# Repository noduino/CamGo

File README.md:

# CamGo
Smart Home Dog to monitor 315&433MHz Sensors, Switches ...

Sensors:

  * door open sensor
  * wireless door bell
  * smoke detection (wireless alarm)
  * gas detection (wireless alarm)
  * wind & rain sensor
  ......

Switchs:

  * 315/433 light switch
  * dooya curtion
  * automatic window
  ......

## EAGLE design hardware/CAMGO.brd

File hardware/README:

Copyright 2015 MaiKe Labs

These files are part of CamGo.

This is a free hardware design; you can redistribute it and/or modify
it under the terms of the GNU General Public License as published by
the Free Software Foundation; either version 2, or (at your option)
any later version.

This design is distributed in the hope that it will be useful,
but WITHOUT ANY WARRANTY; without even the implied warranty of
MERCHANTABILITY or FITNESS FOR A PARTICULAR PURPOSE.  See the
GNU General Public License for more details.

You should have received a copy of the GNU General Public License
along with this design; see the file COPYING.  If not, write to
the Free Software Foundation, Inc., 51 Franklin Street,
Boston, MA 02110-1301, USA.

CamGo is a Smart Home Gateway for 315MHz, 433MHz Sensors and Switches 

hardware notes:

Schematic and layout files were designed in Eagle.

PCB description: 2 layer PCB 0.062 in
    Copper        1   0.5 oz foil plated to approximately 0.0017 in
    Copper        2   0.5 oz foil plated to approximately 0.0017 in

FR4 or similar substrate with Er=4.5 (+/- 0.1)
double side solder mask green
single side silkscreen white
6 mil min trace width and
6 mil min isolation

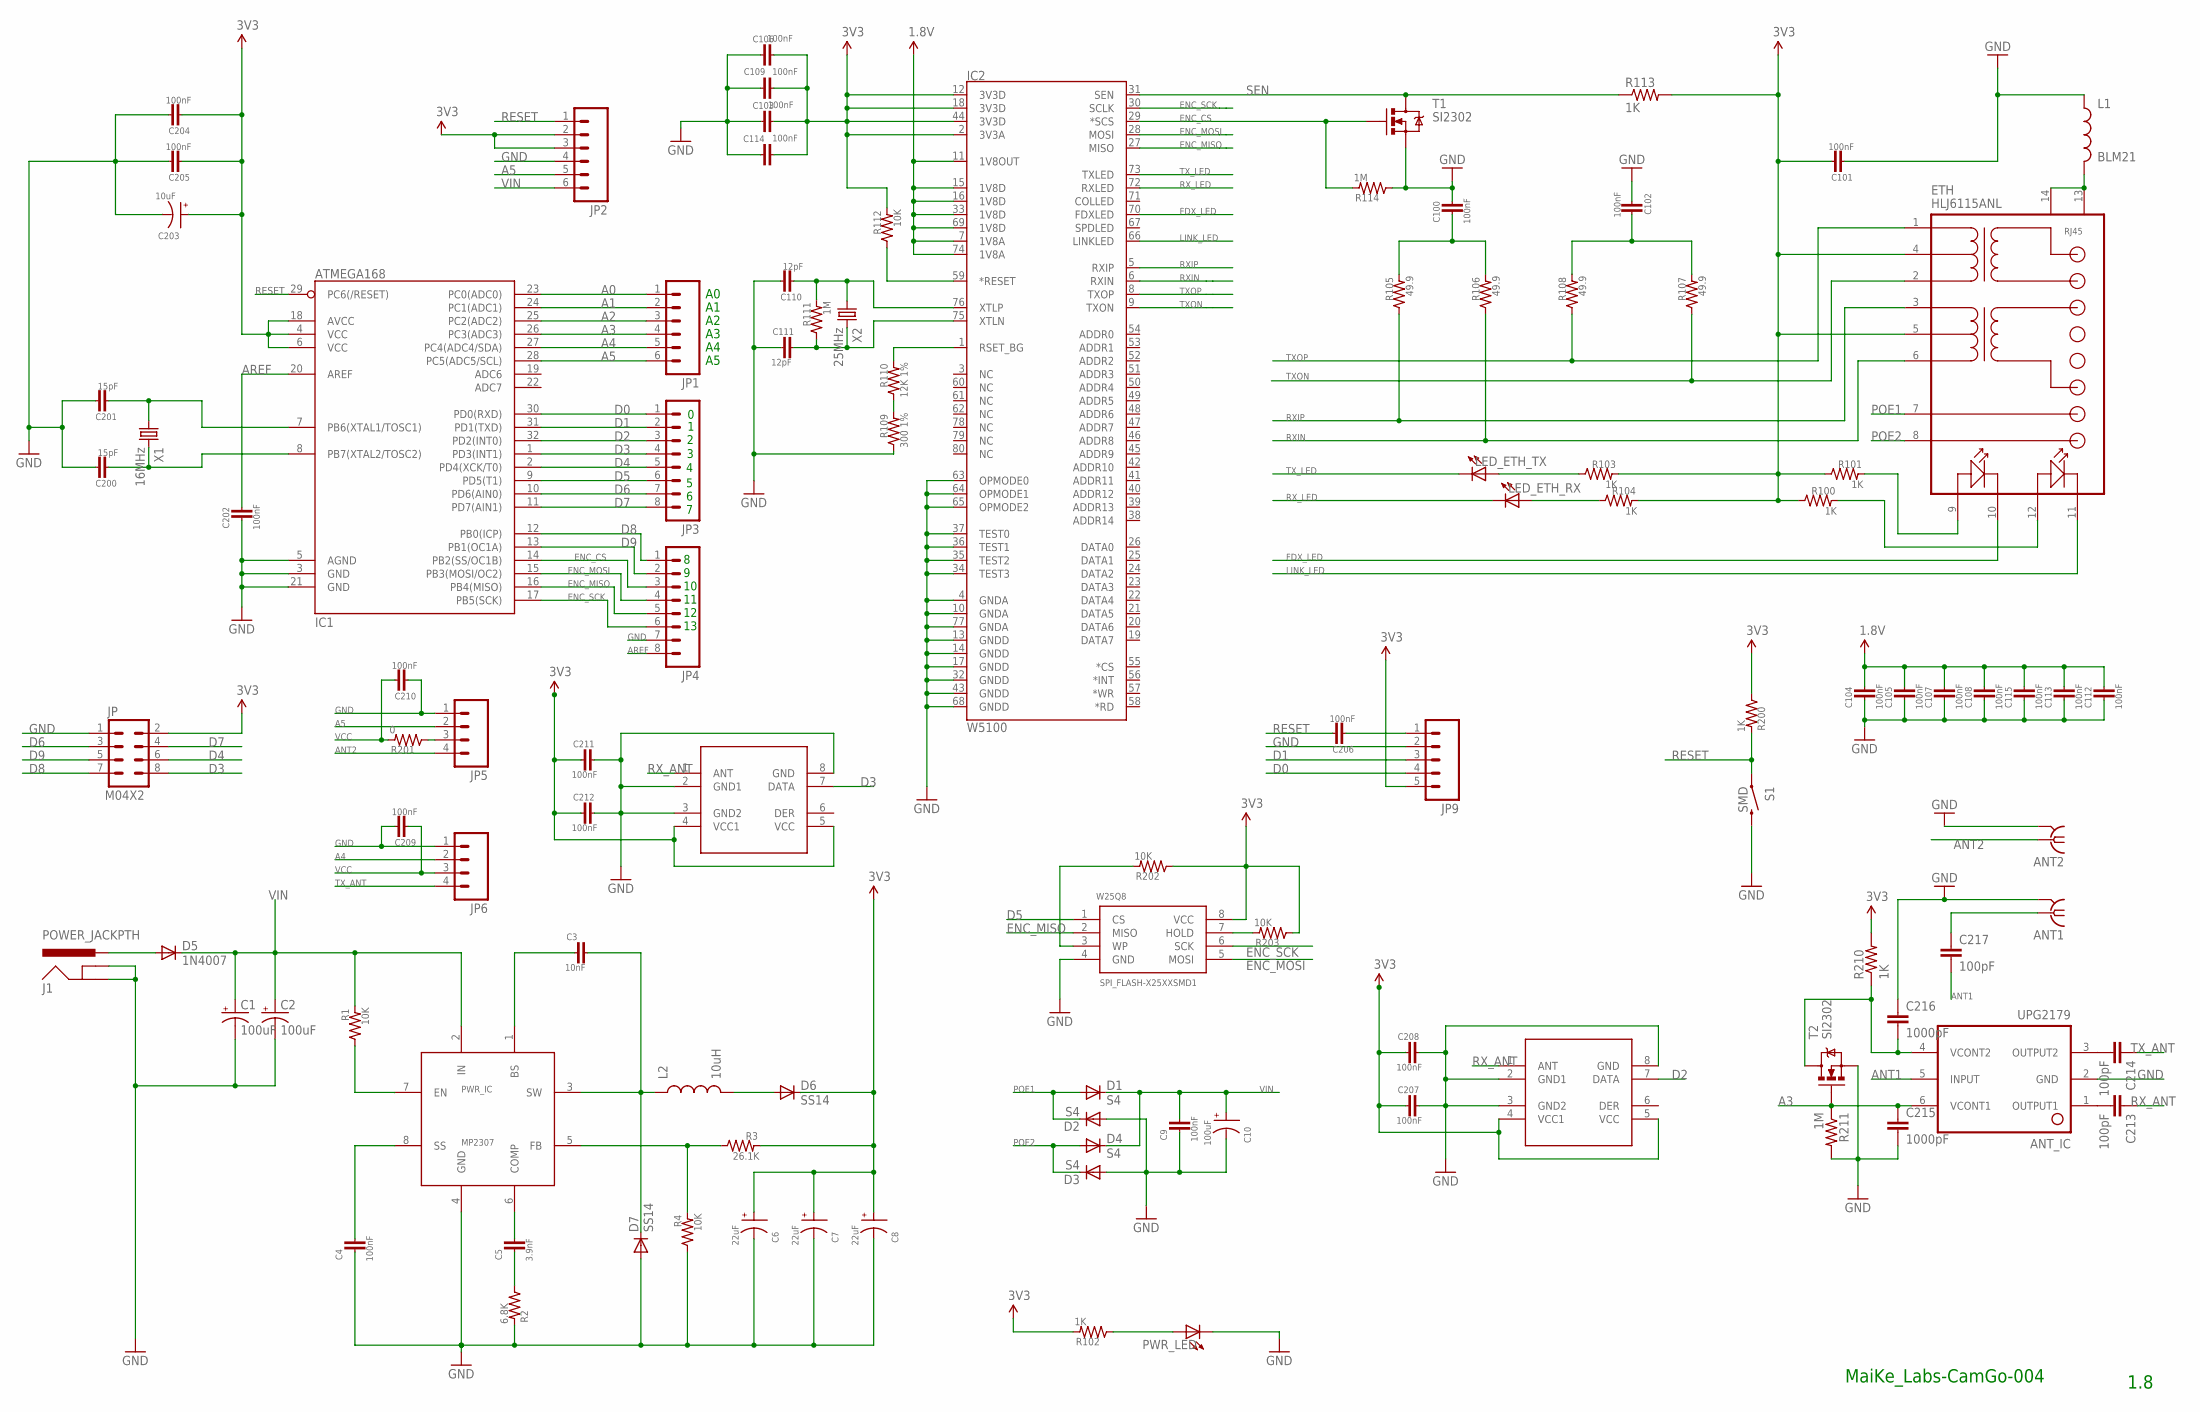
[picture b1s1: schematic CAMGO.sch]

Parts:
ANT1, ANT2: SMA--KE; SMA-KE
ANT_IC: UPG2179; SOT363
C1, C2, C10: 100uF; NIPPON_F80
C3: 10nF; 0603-CAP
C4, C9, C100, C101, C102, C103, C104, C105, C106, C107, C108, C109, C112, C113, C114, C115, C202, C204, C205, C206, C207, C208, C209, C210, C211, C212: 100nF; 0603-CAP
C5: 3.9nF; 0603-CAP
C6, C7, C8: 22uF; EIA3216
C110, C111: 12pF; 0603-CAP
C200, C201: 15pF; 0603-CAP
C203: 10uF; EIA3216
C213, C214, C217: 100pF; 0603-CAP
C215, C216: 1000pF; 0603-CAP
D1, D2, D3, D4: S4; SOD-323
D5: 1N4007; SMB-DIODE
D6, D7: SS14; SOD-323
ETH: HLJ6115ANL; HR911105A
IC1: ATMEGA168; TQFP32-08
IC2: W5100; LQFP-80
J1: POWER_JACKPTH; POWER_JACK_PTH
JP: M04X2; 2X4
JP1, JP2: M06SIP; 1X06
JP3, JP4: M081X08; 1X08
JP5, JP6: M04PTH; 1X04
JP9: M05PTH; 1X05
L1: BLM21; 0805
L2: 10uH; CR54
LED_ETH_RX: LED0603; LED-0603
LED_ETH_TX: LED0603; LED-0603
PWR_IC: MP2307; SOIC8
PWR_LED: LED0603; LED-0603
R1, R4, R112, R202, R203: 10K; 0603-RES
R2: 6.8K; 0603-RES
R3: 26.1K; 0603-RES
R100, R101, R102, R103, R104, R113, R200, R210: 1K; 0603-RES
R105, R106, R107, R108: 49.9; 0603-RES
R109: 300 1%; 0603-RES
R110: 12K 1%; 0603-RES
R111, R114, R211: 1M; 0603-RES
R201: 0; 0603-RES
RX_IC1, RX_IC2: RXB6-MODULE
S1: SMD; TACTILE-SWITCH-1101NE
T1, T2: SI2302; SOT23-3
W25Q8: SPI_FLASH-X25XXSMD1; SO08-EIAJ
X1: 16MHz; HC49US
X2: 25MHz; HC49US

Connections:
1.8V: C104.1, C105.1, C107.1, C108.1, C112.1, C113.1, C115.1, IC2.7 (1V8A), IC2.11 (1V8OUT), IC2.15 (1V8D), IC2.16 (1V8D), IC2.33 (1V8D), IC2.69 (1V8D), IC2.74 (1V8A)
A0: IC1.23 (PC0(ADC0)), JP1.1
A1: IC1.24 (PC1(ADC1)), JP1.2
A2: IC1.25 (PC2(ADC2)), JP1.3
A3: ANT_IC.6 (VCONT1), C215.1, IC1.26 (PC3(ADC3)), JP1.4, R211.1, T2.1 (G)
A4: IC1.27 (PC4(ADC4/SDA)), JP1.5, JP6.2
A5: IC1.28 (PC5(ADC5/SCL)), JP1.6, JP2.5, JP5.2
ANT1: ANT_IC.5 (INPUT), C217.2
ANT2: ANT2.1, JP5.4
AREF: C202.1, IC1.20 (AREF), JP4.8
D0: IC1.30 (PD0(RXD)), JP3.1, JP9.4
D1: IC1.31 (PD1(TXD)), JP3.2, JP9.3
D2: IC1.32 (PD2(INT0)), JP3.3, RX_IC1.7 (DATA)
D3: IC1.1 (PD3(INT1)), JP.8, JP3.4, RX_IC2.7 (DATA)
D4: IC1.2 (PD4(XCK/T0)), JP.6, JP3.5
D5: IC1.9 (PD5(T1)), JP3.6, W25Q8.1 (CS)
D6: IC1.10 (PD6(AIN0)), JP.3, JP3.7
D7: IC1.11 (PD7(AIN1)), JP.4, JP3.8
D8: IC1.12 (PB0(ICP)), JP.7, JP4.1
D9: IC1.13 (PB1(OC1A)), JP.5, JP4.2
ENC_CS: IC1.14 (PB2(SS/OC1B)), IC2.29 (*SCS), JP4.3, R114.2, T1.1 (G)
ENC_MISO: IC1.16 (PB4(MISO)), IC2.27 (MISO), JP4.5, W25Q8.2 (MISO)
ENC_MOSI: IC1.15 (PB3(MOSI/OC2)), IC2.28 (MOSI), JP4.4, W25Q8.5 (MOSI)
ENC_SCK: IC1.17 (PB5(SCK)), IC2.30 (SCLK), JP4.6, W25Q8.6 (SCK)
FDX_LED: ETH.10, IC2.70 (FDXLED)
GND: ANT1.G@1 (GND), ANT1.G@2 (GND), ANT1.G@3 (GND), ANT1.G@4 (GND), ANT2.G@1 (GND), ANT2.G@2 (GND), ANT2.G@3 (GND), ANT2.G@4 (GND), ANT_IC.2 (GND), C1.-, C2.-, C4.2, C6.C (-), C7.C (-), C8.C (-), C9.2, C10.-, C100.1, C101.2, C102.2, C103.2, C104.2, C105.2, C106.2, C107.2, C108.2, C109.1, C110.1, C111.2, C112.2, C113.2, C114.1, C115.2, C200.1, C201.1, C202.2, C203.C (-), C204.1, C205.1, C207.1, C208.1, C209.1, C210.2, C211.1, C212.1, C215.2, C216.1, D2.2 (A), D3.2 (A), D7.2 (A), IC1.3 (GND), IC1.5 (AGND), IC1.21 (GND), IC2.4 (GNDA), IC2.10 (GNDA), IC2.13 (GNDD), IC2.14 (GNDD), IC2.17 (GNDD), IC2.32 (GNDD), IC2.34 (TEST3), IC2.35 (TEST2), IC2.36 (TEST1), IC2.37 (TEST0), IC2.43 (GNDD), IC2.63 (OPMODE0), IC2.64 (OPMODE1), IC2.65 (OPMODE2), IC2.68 (GNDD), IC2.77 (GNDA), J1.GND, J1.GNDBREAK, JP.1, JP2.4, JP4.7, JP5.1, JP6.1, JP9.2, L1.1, PWR_IC.4 (GND), PWR_LED.C, R2.2, R4.1, R109.1, R114.1, R211.2, RX_IC1.2 (GND1), RX_IC1.3 (GND2), RX_IC1.8 (GND), RX_IC2.2 (GND1), RX_IC2.3 (GND2), RX_IC2.8 (GND), S1.P$2 (2), T1.2 (S), T2.2 (S), W25Q8.4 (GND)
LINK_LED: ETH.11, IC2.66 (LINKLED)
unnamed: ETH.9, R101.2
unnamed: C201.2, IC1.7 (PB6(XTAL1/TOSC1)), X1.1
unnamed: C200.2, IC1.8 (PB7(XTAL2/TOSC2)), X1.2
unnamed: C110.2, IC2.76 (XTLP), R111.2, X2.1
unnamed: R202.2, W25Q8.3 (WP)
unnamed: C206.2, JP9.1
unnamed: D5.A, J1.PWR
unnamed: C111.1, IC2.75 (XTLN), R111.1, X2.2
unnamed: C3.2, PWR_IC.1 (BS)
unnamed: PWR_IC.7 (EN), R1.1
unnamed: PWR_LED.A, R102.1
unnamed: C4.1, PWR_IC.8 (SS)
unnamed: IC2.1 (RSET_BG), R110.2
unnamed: R109.2, R110.1
unnamed: ETH.12, R100.2
unnamed: PWR_IC.5 (FB), R3.1, R4.2
unnamed: C102.1, R107.2, R108.2
unnamed: C5.1, PWR_IC.6 (COMP)
unnamed: C5.2, R2.1
unnamed: C3.1, D7.1 (C), L2.P$1 (1), PWR_IC.3 (SW)
unnamed: LED_ETH_TX.A, R103.1
unnamed: C100.2, R105.2, R106.2
unnamed: LED_ETH_RX.A, R104.1
unnamed: D6.2 (A), L2.P$2 (2)
unnamed: JP5.3, R201.1
unnamed: R203.2, W25Q8.7 (HOLD)
unnamed: ETH.13, ETH.14, L1.2
unnamed: ANT_IC.4 (VCONT2), C216.2, R210.1, T2.3 (D)
unnamed: ANT1.1, C217.1
unnamed: ANT_IC.1 (OUTPUT1), C213.2
unnamed: ANT_IC.3 (OUTPUT2), C214.2
POE1: D1.2 (A), D2.1 (C), ETH.7
POE2: D3.1 (C), D4.2 (A), ETH.8
RESET: C206.1, IC1.29 (PC6(/RESET)), IC2.59 (*RESET), JP2.1, R112.1, R200.2, S1.P$1 (1)
RXIN: ETH.6, IC2.6 (RXIN), R106.1
RXIP: ETH.3, IC2.5 (RXIP), R105.1
RX_ANT: C213.1, RX_IC1.1 (ANT), RX_IC2.1 (ANT)
RX_LED: IC2.72 (RXLED), LED_ETH_RX.C
SEN: IC2.31 (SEN), R113.1, T1.3 (D)
TXON: ETH.2, IC2.9 (TXON), R107.1
TXOP: ETH.1, IC2.8 (TXOP), R108.1
TX_ANT: C214.1, JP6.4
TX_LED: IC2.73 (TXLED), LED_ETH_TX.C
VCC: C6.A (+), C7.A (+), C8.A (+), C101.1, C103.1, C106.1, C109.2, C114.2, C203.A (+), C204.2, C205.2, C207.2, C208.2, C209.2, C210.1, C211.2, C212.2, D6.1 (C), ETH.4, ETH.5, IC1.4 (VCC), IC1.6 (VCC), IC1.18 (AVCC), IC2.2 (3V3A), IC2.12 (3V3D), IC2.18 (3V3D), IC2.44 (3V3D), JP.2, JP2.2, JP2.3, JP6.3, JP9.5, R3.2, R100.1, R101.1, R102.2, R103.2, R104.2, R112.2, R113.2, R200.1, R201.2, R202.1, R203.1, R210.2, RX_IC1.4 (VCC1), RX_IC1.5 (VCC), RX_IC2.4 (VCC1), RX_IC2.5 (VCC), W25Q8.8 (VCC)
VIN: C1.+, C2.+, C9.1, C10.+, D1.1 (C), D4.1 (C), D5.C, JP2.6, PWR_IC.2 (IN), R1.2

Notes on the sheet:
MaiKe_Labs-CamGo-004
1.8

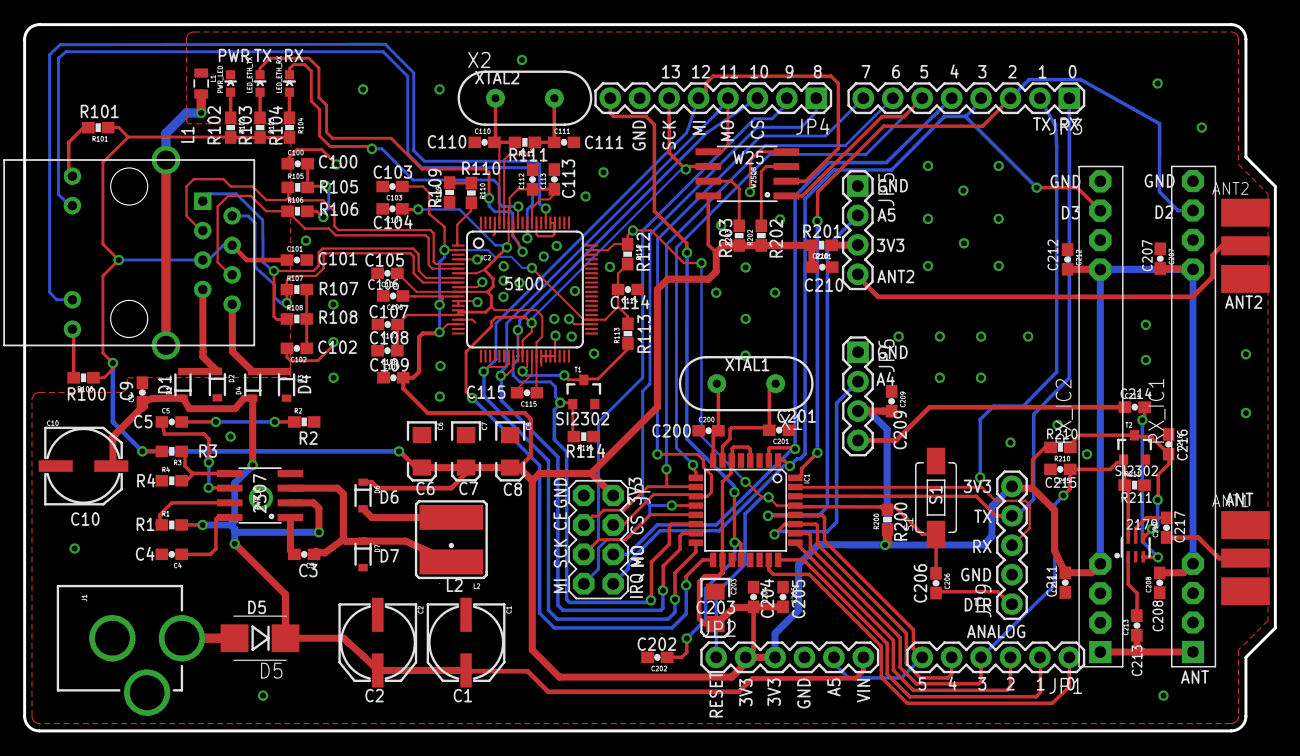
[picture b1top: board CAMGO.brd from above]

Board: 2 copper layers, 108.0 x 61.0 mm, 105 parts (0 on the bottom side), 72 nets.

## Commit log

2015-04-16 add hardware readme
2015-04-16 hw: add the pcb sch file of camgo
    CAMGO.sch is the eagle format
    CAMGO-SCH.png is the png file exported from eagle
2015-04-16 hw: add the layout file of camgo
    CAMGO.brd is the eagle format file
    CAMGO-BRD.png is the png file exported from eagle
2015-04-17 add a board picture
2015-06-30 update the readme
2015-06-30 add a ABS/PLA shell
    It can be printed by 3D printer. It's designed by Yongli He (hyl)
2015-06-30 add the picture of dogy shell
2015-07-03 add the CAD files of official metal shell
    The front panel and rear panel need to order.
    The size of basic shell is 110x70x24mm. You can buy it from:
    http://item.taobao.com/item.htm?id=10605588774
2015-07-16 firmware: add the offical firmware 1.1.6
2015-07-16 doc: add the datasheet used by CamGo
2015-11-02 add the user manual of the procduct camgo
